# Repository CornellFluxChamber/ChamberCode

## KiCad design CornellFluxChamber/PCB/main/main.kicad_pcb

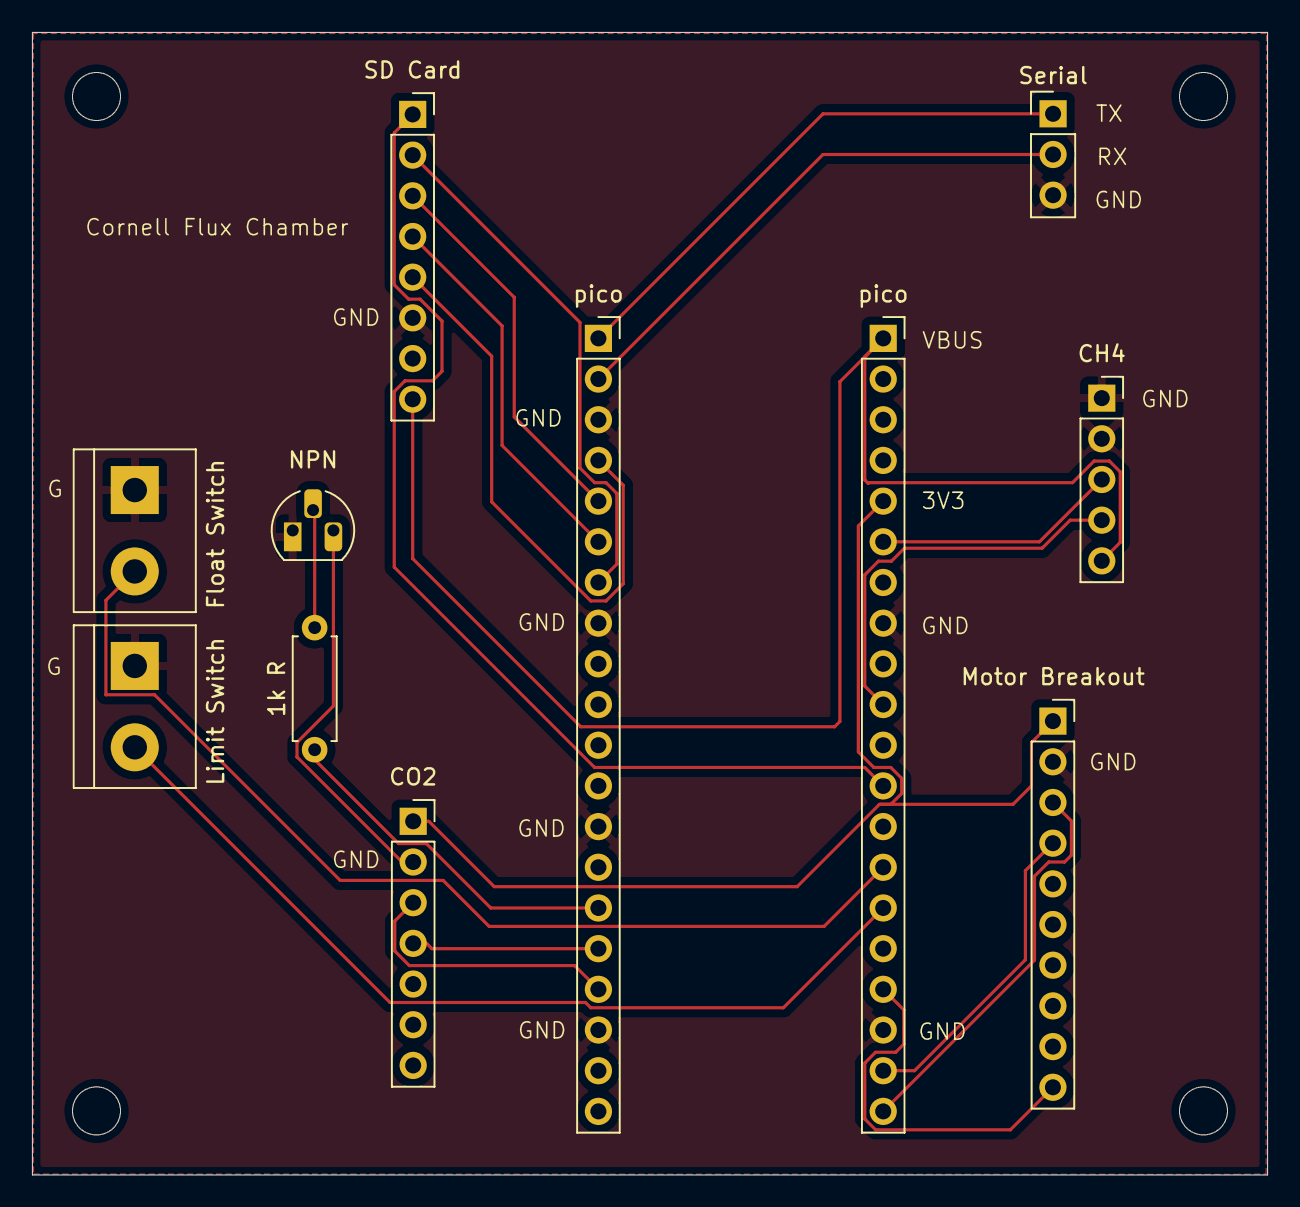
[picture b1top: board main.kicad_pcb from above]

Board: 2 copper layers, 77.1 x 71.3 mm, 11 parts (0 on the bottom side), 22 nets.

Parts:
1k R: 1k; R_Axial_DIN0207_L6.3mm_D2.5mm_P7.62mm_Horizontal
CH4: Methane; PinSocket_1x05_P2.54mm_Vertical
CO2: CO2; PinSocket_1x07_P2.54mm_Vertical
Float Switch: float switch; TerminalBlock_bornier-2_P5.08mm
Limit Switch: limit switch; TerminalBlock_bornier-2_P5.08mm
Motor Breakout: motor_breakout; PinSocket_1x10_P2.54mm_Vertical
NPN: 2N3904; TO-92_HandSolder
SD Card: SD_card; PinSocket_1x08_P2.54mm_Vertical
Serial: uart breakout; PinHeader_1x03_P2.54mm_Vertical
pico: rp2040_1; PinSocket_1x20_P2.54mm_Vertical
pico#2: rp2040_2; PinSocket_1x20_P2.54mm_Vertical

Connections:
GND: CH4.1, CH4.2, Float Switch.1, Limit Switch.1, Motor Breakout.2, NPN.1 (E), SD Card.6, Serial.3, pico.8, pico.18, pico#2.3, pico#2.8, pico#2.13, pico#2.18
unnamed: CO2.1, Motor Breakout.1, pico.5
unnamed: Motor Breakout.3, pico.20
unnamed: Motor Breakout.4, pico.19
unnamed: Motor Breakout.10, pico.17
unnamed: Limit Switch.2, pico.15
unnamed: Float Switch.2, pico.14
unnamed: CH4.3, pico.6
unnamed: CH4.4, pico.10
unnamed: CH4.5, SD Card.8, pico.1
unnamed: CO2.2, NPN.3 (C)
unnamed: CO2.3, pico#2.17
unnamed: CO2.4, pico#2.16
unnamed: SD Card.1, pico.12
unnamed: SD Card.2, pico#2.7
unnamed: SD Card.3, pico#2.5
unnamed: SD Card.4, pico#2.6
unnamed: SD Card.5, pico#2.4
unnamed: Serial.1, pico#2.1
unnamed: Serial.2, pico#2.2
unnamed: 1k R.1, pico#2.15
unnamed: 1k R.2, NPN.2 (B)

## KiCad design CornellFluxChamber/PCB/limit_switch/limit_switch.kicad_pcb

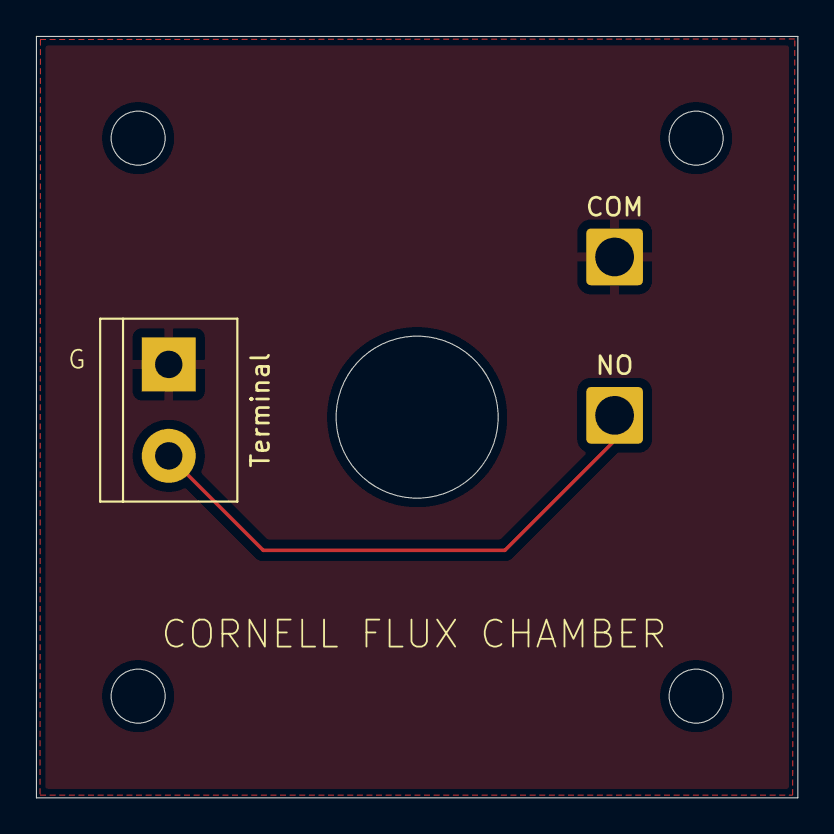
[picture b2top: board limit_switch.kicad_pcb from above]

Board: 2 copper layers, 42.3 x 42.3 mm, 3 parts (0 on the bottom side), 2 nets.

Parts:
COM: COM; SolderWire-1.5sqmm_1x01_D1.7mm_OD3mm
NO: NO; SolderWire-1.5sqmm_1x01_D1.7mm_OD3mm
Terminal: screw terminal 1; TerminalBlock_bornier-2_P5.08mm

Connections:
GND: COM.1, Terminal.1
unnamed: NO.1, Terminal.2

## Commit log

2025-08-15 summer prototype
2025-11-08 add laser cut templates
2025-11-11 sequence updates
2025-12-05 removing unnecessary files
2025-12-13 prepare for handoff
2025-12-13 add PCB files
2025-12-18 reorganize repo
2025-12-18 remove .DS_Store
